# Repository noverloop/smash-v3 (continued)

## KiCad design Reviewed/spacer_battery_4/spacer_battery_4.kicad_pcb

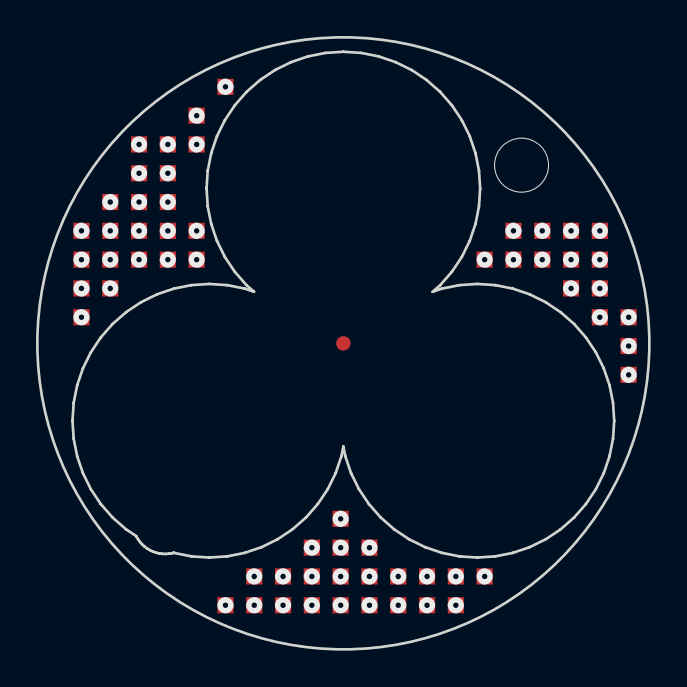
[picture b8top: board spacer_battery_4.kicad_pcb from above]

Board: 2 copper layers, 34.0 x 34.0 mm, 3 parts (1 on the bottom side), 46 nets, no tracks yet.

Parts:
J_spacer_battery_4_top: LGA_lands; J_spacer_battery_4_top
P_spacer_battery_4_bot: LGA_lands; P_spacer_battery_4_bot
SP_battery_4: SP_battery_4; Spacer_Mechanical_34mm

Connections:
3V3: J_spacer_battery_4_top.23, J_spacer_battery_4_top.47, J_spacer_battery_4_top.52, P_spacer_battery_4_bot.23, P_spacer_battery_4_bot.47, P_spacer_battery_4_bot.52
3V3_AON: J_spacer_battery_4_top.24, J_spacer_battery_4_top.48, P_spacer_battery_4_bot.24, P_spacer_battery_4_bot.48
ACTIVATE_CONFIRM: J_spacer_battery_4_top.3, P_spacer_battery_4_bot.3
ACTIVATE_SET: J_spacer_battery_4_top.4, P_spacer_battery_4_bot.4
BAT_PROT: J_spacer_battery_4_top.5, J_spacer_battery_4_top.49, P_spacer_battery_4_bot.5, P_spacer_battery_4_bot.49
BAT_RAW: J_spacer_battery_4_top.6, J_spacer_battery_4_top.50, P_spacer_battery_4_bot.6, P_spacer_battery_4_bot.50
BOOT0: J_spacer_battery_4_top.7, P_spacer_battery_4_bot.7
COMP_5V: J_spacer_battery_4_top.8, J_spacer_battery_4_top.51, P_spacer_battery_4_bot.8, P_spacer_battery_4_bot.51
COMP_SWDCLK: J_spacer_battery_4_top.9, P_spacer_battery_4_bot.9
COMP_SWDIO: J_spacer_battery_4_top.10, P_spacer_battery_4_bot.10
EXT_CAN_RX: J_spacer_battery_4_top.11, P_spacer_battery_4_bot.11
EXT_CAN_TX: J_spacer_battery_4_top.14, P_spacer_battery_4_bot.14
FIN1_AOUT1: J_spacer_battery_4_top.13, P_spacer_battery_4_bot.13
FIN1_AOUT2: J_spacer_battery_4_top.12, P_spacer_battery_4_bot.12
FIN1_BOUT1: J_spacer_battery_4_top.15, P_spacer_battery_4_bot.15
FIN1_BOUT2: J_spacer_battery_4_top.16, P_spacer_battery_4_bot.16
FIN2_AOUT1: J_spacer_battery_4_top.17, P_spacer_battery_4_bot.17
FIN2_AOUT2: J_spacer_battery_4_top.18, P_spacer_battery_4_bot.18
FIN2_BOUT1: J_spacer_battery_4_top.19, P_spacer_battery_4_bot.19
FIN2_BOUT2: J_spacer_battery_4_top.20, P_spacer_battery_4_bot.20
FIN3_AOUT1: J_spacer_battery_4_top.21, P_spacer_battery_4_bot.21
FIN3_AOUT2: J_spacer_battery_4_top.22, P_spacer_battery_4_bot.22
FIN3_BOUT1: J_spacer_battery_4_top.1, P_spacer_battery_4_bot.1
FIN3_BOUT2: J_spacer_battery_4_top.2, P_spacer_battery_4_bot.2
FIN4_AOUT1: J_spacer_battery_4_top.25, P_spacer_battery_4_bot.25
FIN4_AOUT2: J_spacer_battery_4_top.26, P_spacer_battery_4_bot.26
FIN4_BOUT1: J_spacer_battery_4_top.27, P_spacer_battery_4_bot.27
FIN4_BOUT2: J_spacer_battery_4_top.28, P_spacer_battery_4_bot.28
FIN_HALL: J_spacer_battery_4_top.29, P_spacer_battery_4_bot.29
FLEX_GND: J_spacer_battery_4_top.30, J_spacer_battery_4_top.53, J_spacer_battery_4_top.54, J_spacer_battery_4_top.55, J_spacer_battery_4_top.56, J_spacer_battery_4_top.57, J_spacer_battery_4_top.58, J_spacer_battery_4_top.59, J_spacer_battery_4_top.60, P_spacer_battery_4_bot.30, P_spacer_battery_4_bot.53, P_spacer_battery_4_bot.54, P_spacer_battery_4_bot.55, P_spacer_battery_4_bot.56, P_spacer_battery_4_bot.57, P_spacer_battery_4_bot.58, P_spacer_battery_4_bot.59, P_spacer_battery_4_bot.60, SP_battery_4.1
GPIO_EXT_0: J_spacer_battery_4_top.31, P_spacer_battery_4_bot.31
GPIO_EXT_1: J_spacer_battery_4_top.32, P_spacer_battery_4_bot.32
GPIO_EXT_2: J_spacer_battery_4_top.33, P_spacer_battery_4_bot.33
GPIO_EXT_3: J_spacer_battery_4_top.34, P_spacer_battery_4_bot.34
H3LIS_INT1: J_spacer_battery_4_top.35, P_spacer_battery_4_bot.35
I2C3_SCL: J_spacer_battery_4_top.36, P_spacer_battery_4_bot.36
I2C3_SDA: J_spacer_battery_4_top.37, P_spacer_battery_4_bot.37
JUMP_WAKE: J_spacer_battery_4_top.38, P_spacer_battery_4_bot.38
NRST: J_spacer_battery_4_top.39, P_spacer_battery_4_bot.39
SWO: J_spacer_battery_4_top.40, P_spacer_battery_4_bot.40
SYS_I2C_SCL: J_spacer_battery_4_top.41, P_spacer_battery_4_bot.41
SYS_I2C_SDA: J_spacer_battery_4_top.42, P_spacer_battery_4_bot.42
SYS_SPI_CS_FIN: J_spacer_battery_4_top.43, P_spacer_battery_4_bot.43
SYS_SPI_MISO: J_spacer_battery_4_top.44, P_spacer_battery_4_bot.44
SYS_SPI_MOSI: J_spacer_battery_4_top.45, P_spacer_battery_4_bot.45
SYS_SPI_SCLK: J_spacer_battery_4_top.46, P_spacer_battery_4_bot.46
